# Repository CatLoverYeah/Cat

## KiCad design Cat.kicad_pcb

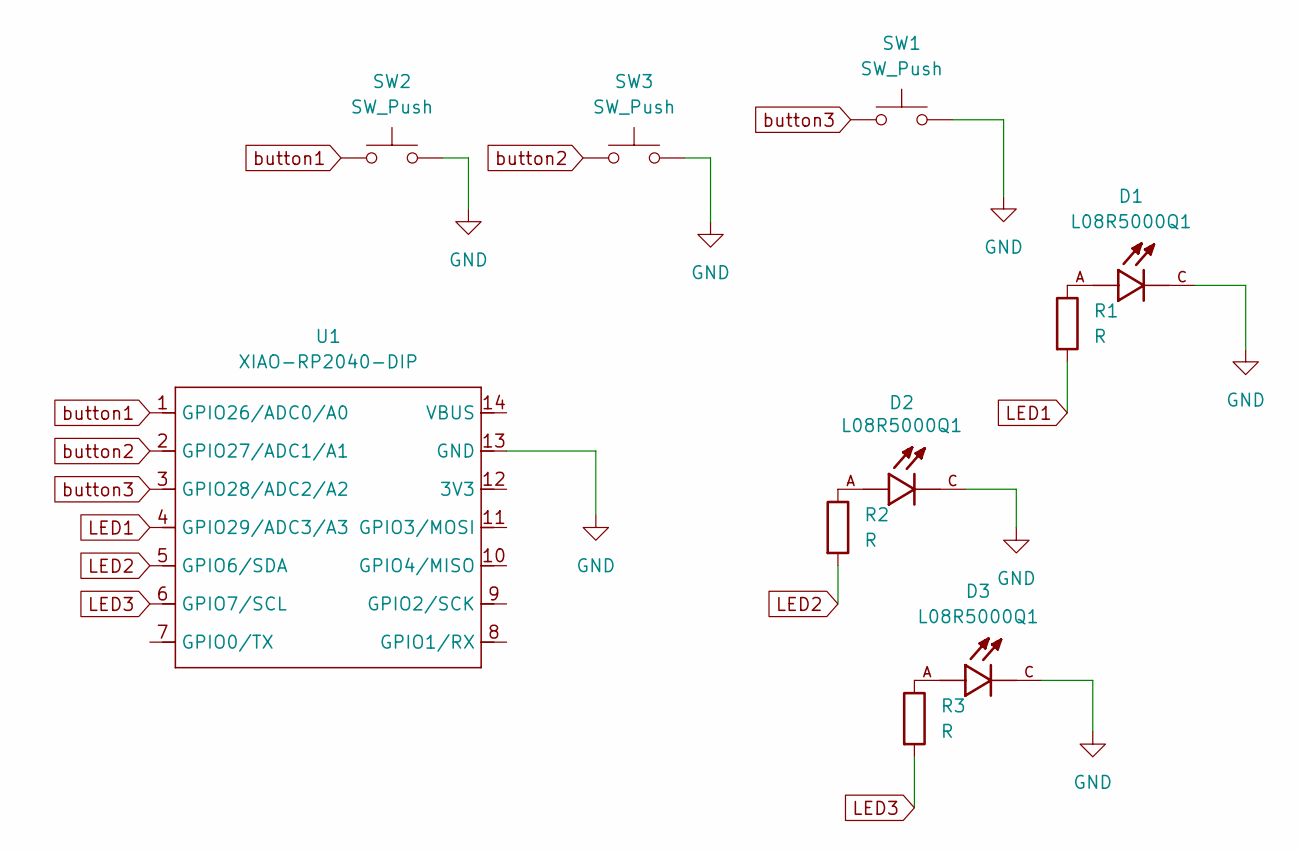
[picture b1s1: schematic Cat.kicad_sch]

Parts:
D1, D2, D3: L08R5000Q1; LEDRD254W57D500H1070; PARTREV NA
R1, R2, R3: R; R_Axial_DIN0204_L3.6mm_D1.6mm_P5.08mm_Horizontal
SW1, SW2, SW3: SW_Push; SW_Cherry_MX_1.00u_PCB
U1: XIAO-RP2040-DIP; XIAO-RP2040-DIP (3)

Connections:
GND: D1.C, D2.C, D3.C, SW1.2, SW2.2, SW3.2, U1.13 (GND)
LED1: R1.2, U1.4 (GPIO29/ADC3/A3)
LED2: R2.2, U1.5 (GPIO6/SDA)
LED3: R3.2, U1.6 (GPIO7/SCL)
unnamed: D1.A, R1.1
unnamed: D2.A, R2.1
unnamed: D3.A, R3.1
button1: SW2.1, U1.1 (GPIO26/ADC0/A0)
button2: SW3.1, U1.2 (GPIO27/ADC1/A1)
button3: SW1.1, U1.3 (GPIO28/ADC2/A2)

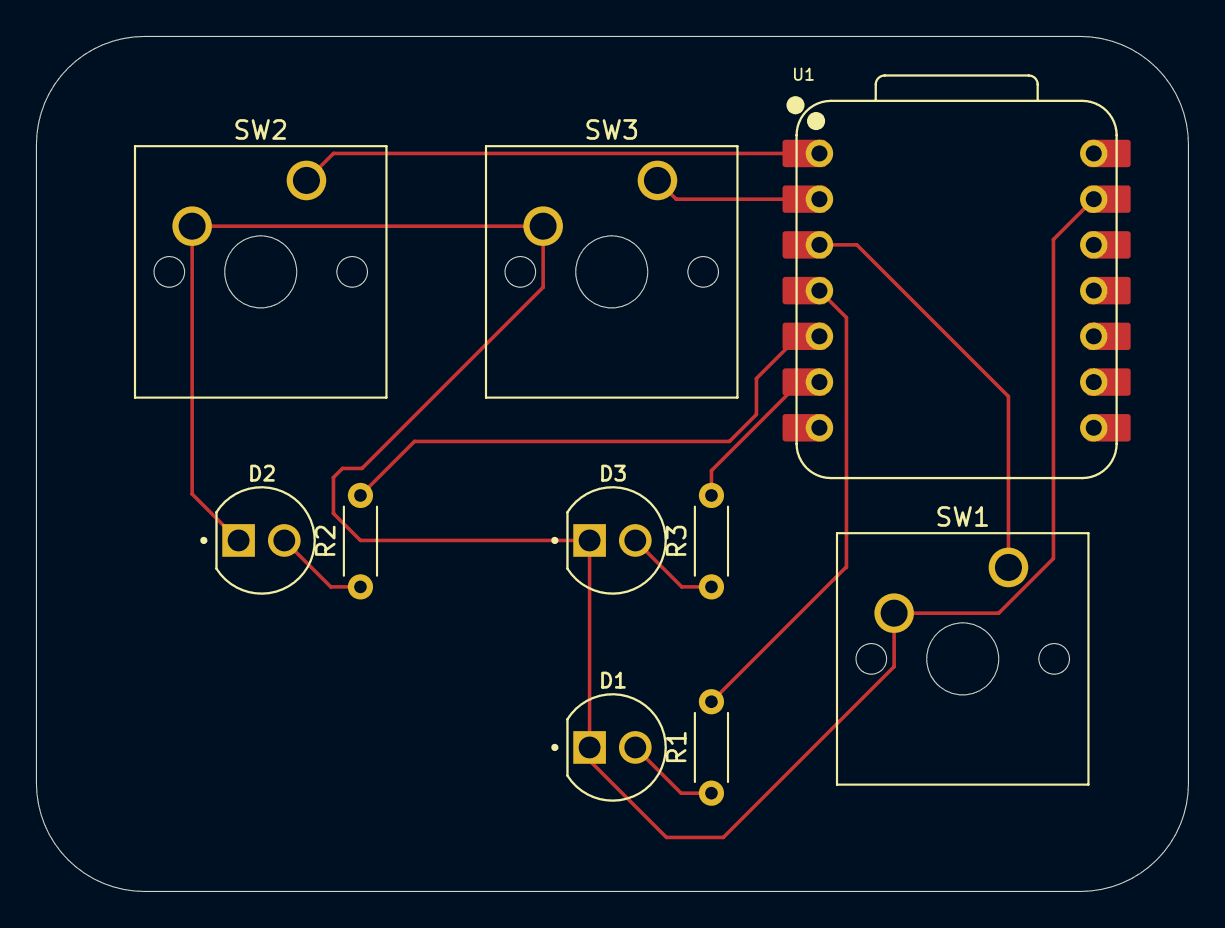
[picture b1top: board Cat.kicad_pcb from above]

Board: 2 copper layers, 64.0 x 47.5 mm, 10 parts (0 on the bottom side), 10 nets.
